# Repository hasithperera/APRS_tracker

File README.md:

# APRS_tracker

Standalone APRS tracker. This an Arduino-nano powered APRS tracker with a DRA818V 1 W radio module.

## Progress

- Fully functional PCB(v2) - tested up to 11 km in a HAB flight
- Basic full operation was tested with the board externally powered. Refer the test section for details.
- v3: Nearly complete PCB with new GPS module
	- level shifter externally added using a 7404 

### Firmware

- [x] Bug fix for location packets
- [x] Support for GNSS GPS (Adafruit GPS) ✅ 2024-01-28
- [x] Added support for i2c for external data sources ✅ 2024-01-28
## Testing 

In order to make sure the full functionality the generated APRS packets were tested with [direwolf](https://github.com/wb2osz/direwolf) with a RTL-SDR.
The following command was used to run the iGate

``` rtl_fm -f 144.39M - |direwolf -c sdr.conf -r 24000 -D 1 - ```

- The radio tx frequency commands were tested on a simplex 145.390 M and the standard 144.390 M
- A ground test was carried out on 05/14/23.
	- Device was powered with a external 5V USB power bank for the duration of the test
	- initial GPS lock was completed within 30 s of powering on outside.
	- It was noted that powering indoor and moving to an outdoor location increased the initial GPS lock time significantly.
	- Data collected is available online under the call sign KC3RXZ. a screenshot can be found below. Note that not all the packets were captured by the iGate and the msg_id was used as a counter for how many GPS packets were captured during the test period.Given that the iGate was located indoor and the landscape of the location could account for the lost packets.

APRS ground testing.

### Flight testing

- First HAB flight on 01/10/2023
- call: KE8TJE-11
- data: [aprs.fi](https://aprs.fi/#!mt=roadmap&z=10&call=a%2FKE8TJE-11&timerange=21600&tail=21600)
- comments: The GPS module used worked well up to 11 km of altitude. above that it was unusable
- more information available [here](https://docs.google.com/presentation/d/1fhy-rmdOGR4Q17i7Nnw9TJokxQfwU8tR1A3V_ZNNeEo/edit?usp=sharing) including flight data

## Updates to the PCB

### update: 05/07/23

- [x] Update PCB based on v1.
- know minor issues
	- jumpers on the board need to be larger

### update: October 2023

- updated the GPS module

### update: January 2034
- New design with an expansion slot to connect external modules.
- A DTMF decoder board is been developed.
- [ ] Final integration testing needs to be done

## Todo list 

- [x] interface GPS sensor
- [x] interface RF
- [x] APRS generation
- [x] get location and update APRS data packet
- [x] i2c slave module to provide data to master ✅ 2024-01-28
- [x] field testing 
- [x] finalized PCB design 
- [x] long range testing at altitude

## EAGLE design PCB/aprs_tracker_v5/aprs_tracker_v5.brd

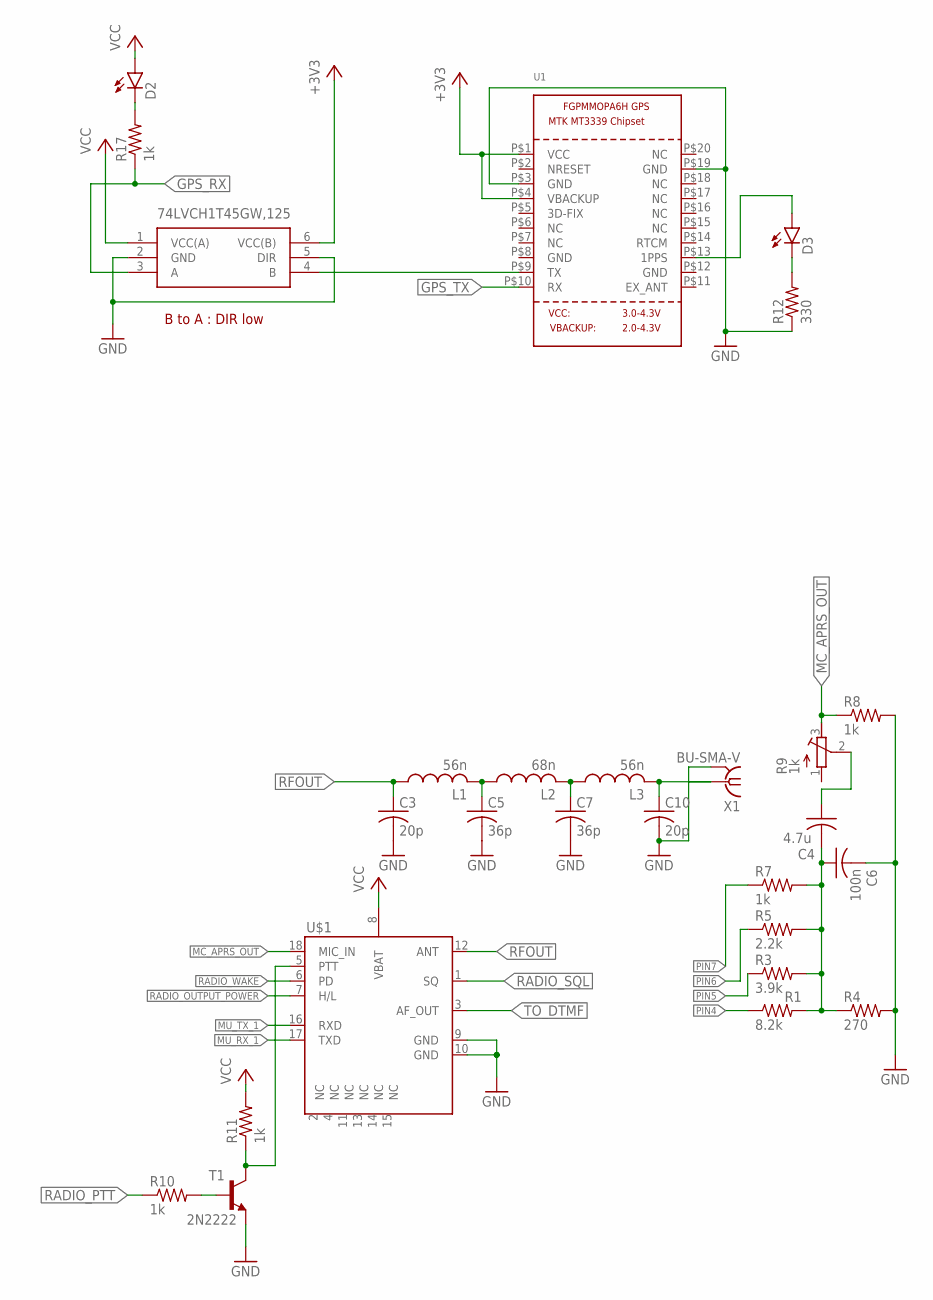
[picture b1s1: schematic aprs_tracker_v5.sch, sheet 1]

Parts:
C3, C10: 20p; C0805K
C4: 4.7u; C0805
C5, C7: 36p; C0805K
C6: 100n; C0805
D2, D3: LEDCHIP-LED0805; CHIP-LED0805
IC3: 74LVCH1T45GW,125; 74LVCH1T45GW125
L1, L3: 56n; L3216C
L2: 68n; L3216C
R1: 8.2k; R0805
R3: 3.9k; R0805
R4: 270; R0805
R5: 2.2k; R0805
R7, R8, R10, R11, R17: 1k; R0805
R9: 1k; RTRIM3339P
R12: 330; R0805
T1: 2N2222; TO92-EBC-OVAL
U1: GPS_FGPMMOPA6H; FGPMMOPA6H
U$1: DRA818A
X1: BU-SMA-V

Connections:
+3V3: IC3.6 (VCC(B)), U1.P$1 (VCC), U1.P$4 (VBACKUP); also elsewhere on the board
GND: C3.2, C5.2, C6.2, C7.2, C10.2, IC3.2 (GND), IC3.5 (DIR), R4.2, R8.2, R12.1, T1.E, U1.P$3 (GND), U1.P$19 (GND), U$1.9 (GND), U$1.10 (GND), X1.2, X1.3 (2), X1.4 (2), X1.5 (2); also elsewhere on the board
GPS_RX: IC3.3 (A), R17.1; also elsewhere on the board
GPS_TX: U1.P$10 (RX); also elsewhere on the board
MC_APRS_OUT: R8.1, R9.3 (E), U$1.18 (MIC_IN); also elsewhere on the board
MU_RX_1: U$1.17 (TXD); also elsewhere on the board
MU_TX_1: U$1.16 (RXD); also elsewhere on the board
unnamed: IC3.4 (B), U1.P$9 (TX)
unnamed: C5.1, L1.2, L2.1
unnamed: C7.1, L2.2, L3.1
unnamed: C10.1, L3.2, X1.1
unnamed: D2.C, R17.2
unnamed: C4.2, C6.1, R1.2, R3.2, R4.1, R5.2, R7.2
unnamed: C4.1, R9.2 (S)
unnamed: R11.1, T1.C, U$1.5 (PTT)
unnamed: R10.2, T1.B
unnamed: D3.C, R12.2
unnamed: D3.A, U1.P$13 (1PPS)
PIN4: R1.1; also elsewhere on the board
PIN5: R3.1; also elsewhere on the board
PIN6: R5.1; also elsewhere on the board
PIN7: R7.1; also elsewhere on the board
RADIO_OUTPUT_POWER: U$1.7 (H/L); also elsewhere on the board
RADIO_PTT: R10.1; also elsewhere on the board
RADIO_SQL: U$1.1 (SQ); also elsewhere on the board
RADIO_WAKE: U$1.6 (PD); also elsewhere on the board
RFOUT: C3.1, L1.1, U$1.12 (ANT)
TO_DTMF: U$1.3 (AF_OUT); also elsewhere on the board
VCC: D2.A, IC3.1 (VCC(A)), R11.2, U$1.8 (VBAT); also elsewhere on the board

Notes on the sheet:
B to A : DIR low

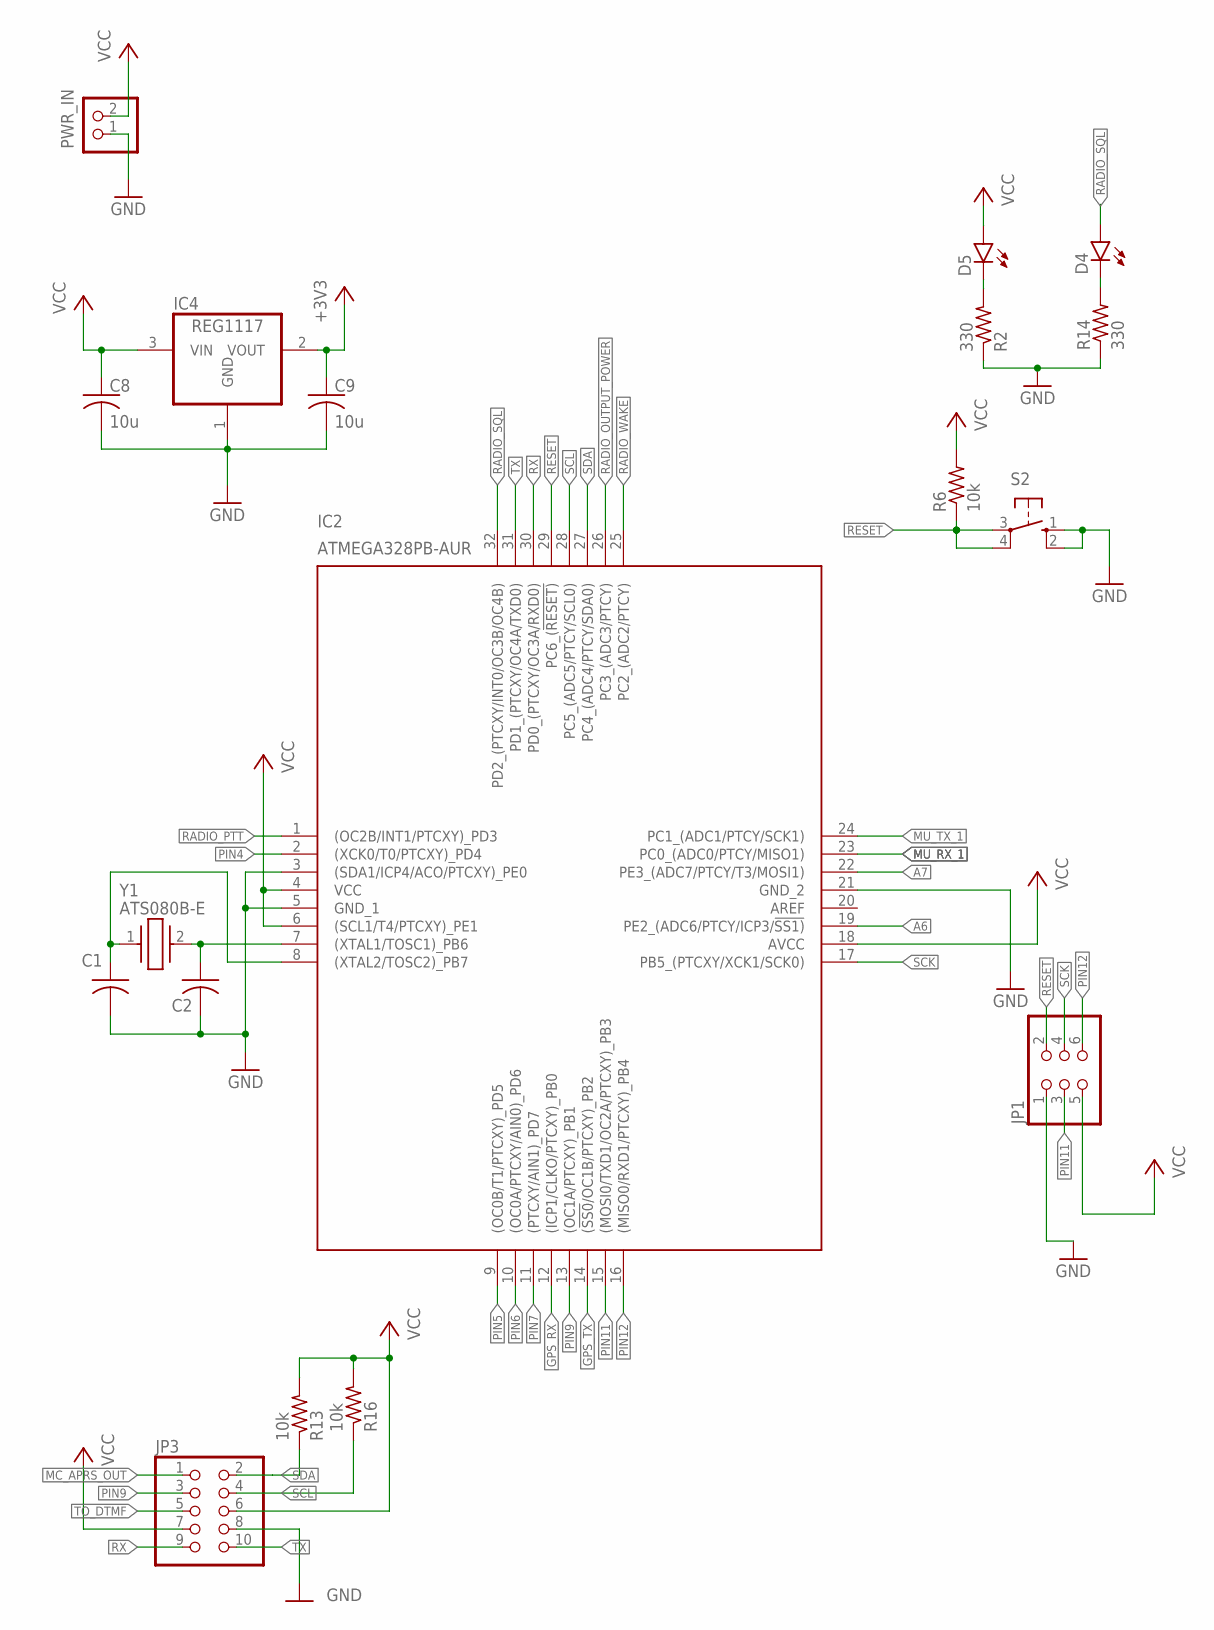
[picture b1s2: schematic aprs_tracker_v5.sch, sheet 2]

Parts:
C1, C2: C-USC0805; C0805
C8, C9: 10u; C0805
D4, D5: LEDCHIP-LED0805; CHIP-LED0805
IC2: ATMEGA328PB-AUR; QFP80P900X900X120-32N
IC4: REG1117; SOT223
JP1: PINHD-2X3; 2X03
JP3: PINHD-2X5; 2X05
PWR_IN: PINHD-1X2; 1X02
R2, R14: 330; R0805
R6, R13, R16: 10k; R0805
S2: 10-XX; B3F-10XX
Y1: ATS080B-E; ATS080BE

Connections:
+3V3: C9.1, IC4.2 (VOUT); also elsewhere on the board
A6: IC2.19 (PE2_(ADC6/PTCY/ICP3/!SS1))
A7: IC2.22 (PE3_(ADC7/PTCY/T3/MOSI1))
GND: C1.2, C2.2, C8.2, C9.2, IC2.3 ((SDA1/ICP4/ACO/PTCXY)_PE0), IC2.5 (GND_1), IC2.21 (GND_2), IC4.1 (GND), JP1.1, JP3.8, PWR_IN.1, R2.1, R14.1, S2.1 (S), S2.2 (S1); also elsewhere on the board
GPS_RX: IC2.12 ((ICP1/CLKO/PTCXY)_PB0); also elsewhere on the board
GPS_TX: IC2.14 ((!SS0!/OC1B/PTCXY)_PB2); also elsewhere on the board
MC_APRS_OUT: JP3.1; also elsewhere on the board
MU_RX_1: IC2.23 (PC0_(ADC0/PTCY/MISO1)); also elsewhere on the board
MU_TX_1: IC2.24 (PC1_(ADC1/PTCY/SCK1)); also elsewhere on the board
unnamed: D5.C, R2.2
unnamed: C1.1, IC2.8 ((XTAL2/TOSC2)_PB7), Y1.1
unnamed: C2.1, IC2.7 ((XTAL1/TOSC1)_PB6), Y1.2
unnamed: D4.C, R14.2
PIN4: IC2.2 ((XCK0/T0/PTCXY)_PD4); also elsewhere on the board
PIN5: IC2.9 ((OC0B/T1/PTCXY)_PD5); also elsewhere on the board
PIN6: IC2.10 ((OC0A/PTCXY/AIN0)_PD6); also elsewhere on the board
PIN7: IC2.11 ((PTCXY/AIN1)_PD7); also elsewhere on the board
PIN9: IC2.13 ((OC1A/PTCXY)_PB1), JP3.3
PIN11: IC2.15 ((MOSI0/TXD1/OC2A/PTCXY)_PB3), JP1.3
PIN12: IC2.16 ((MISO0/RXD1/PTCXY)_PB4), JP1.6
RADIO_OUTPUT_POWER: IC2.26 (PC3_(ADC3/PTCY)); also elsewhere on the board
RADIO_PTT: IC2.1 ((OC2B/INT1/PTCXY)_PD3); also elsewhere on the board
RADIO_SQL: D4.A, IC2.32 (PD2_(PTCXY/INT0/OC3B/OC4B)); also elsewhere on the board
RADIO_WAKE: IC2.25 (PC2_(ADC2/PTCY)); also elsewhere on the board
RESET: IC2.29 (PC6_(!RESET)), JP1.2, R6.1, S2.3, S2.4 (P1)
RX: IC2.30 (PD0_(PTCXY/OC3A/RXD0)), JP3.9
SCK: IC2.17 (PB5_(PTCXY/XCK1/SCK0)), JP1.4
SCL: IC2.28 (PC5_(ADC5/PTCY/SCL0)), JP3.4, R16.1
SDA: IC2.27 (PC4_(ADC4/PTCY/SDA0)), JP3.2, R13.1
TO_DTMF: JP3.5; also elsewhere on the board
TX: IC2.31 (PD1_(PTCXY/OC4A/TXD0)), JP3.10
VCC: C8.1, D5.A, IC2.4 (VCC), IC2.6 ((SCL1/T4/PTCXY)_PE1), IC2.18 (AVCC), IC4.3 (VIN), JP1.5, JP3.6, JP3.7, PWR_IN.2, R6.2, R13.2, R16.2; also elsewhere on the board

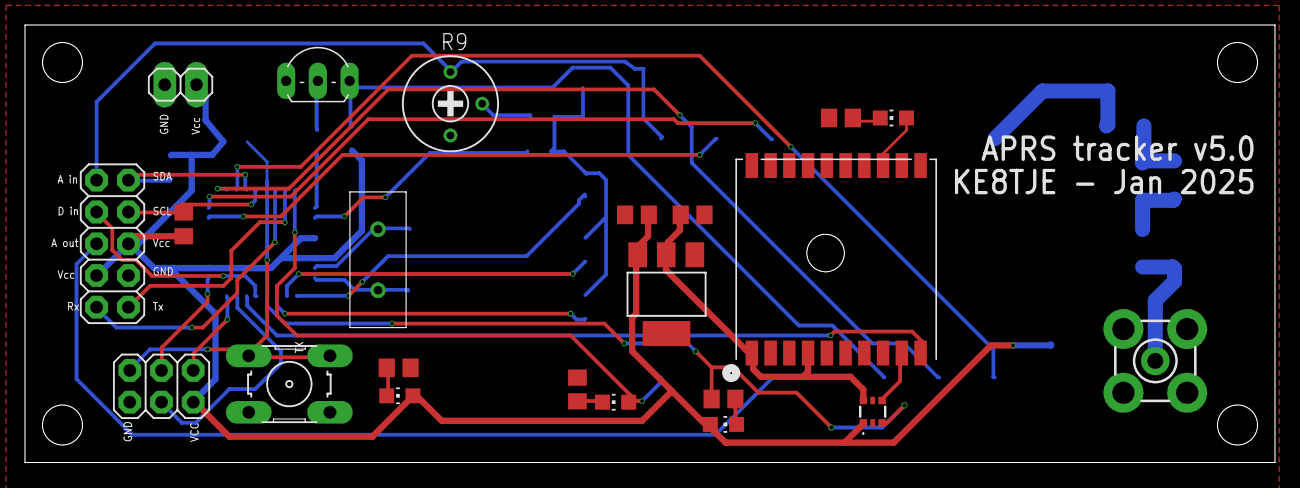
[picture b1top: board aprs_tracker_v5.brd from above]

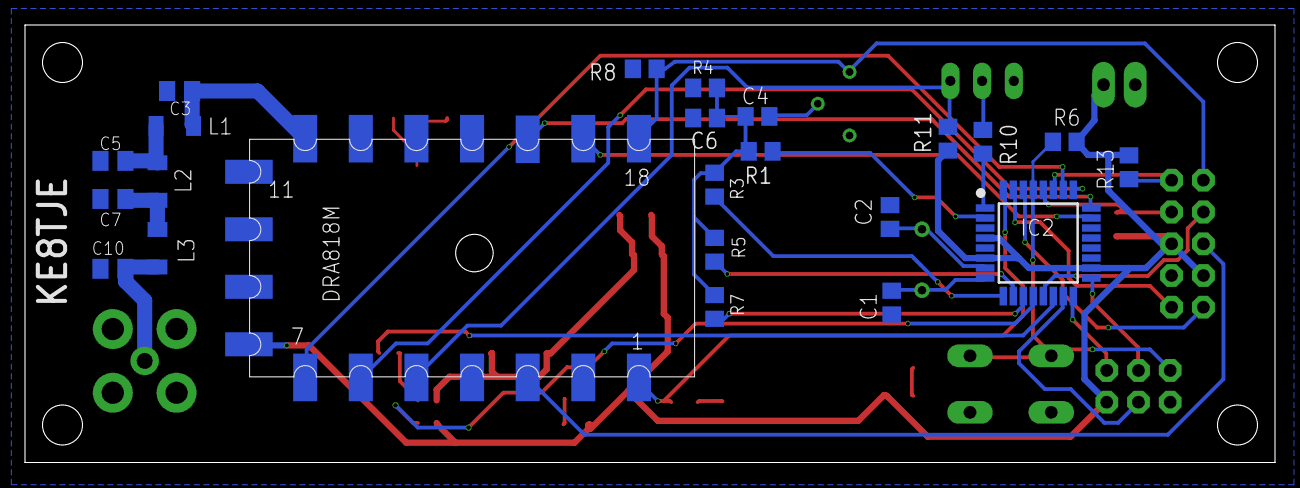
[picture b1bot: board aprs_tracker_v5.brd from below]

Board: 2 copper layers, 100.0 x 35.0 mm, 45 parts (23 on the bottom side), 42 nets.

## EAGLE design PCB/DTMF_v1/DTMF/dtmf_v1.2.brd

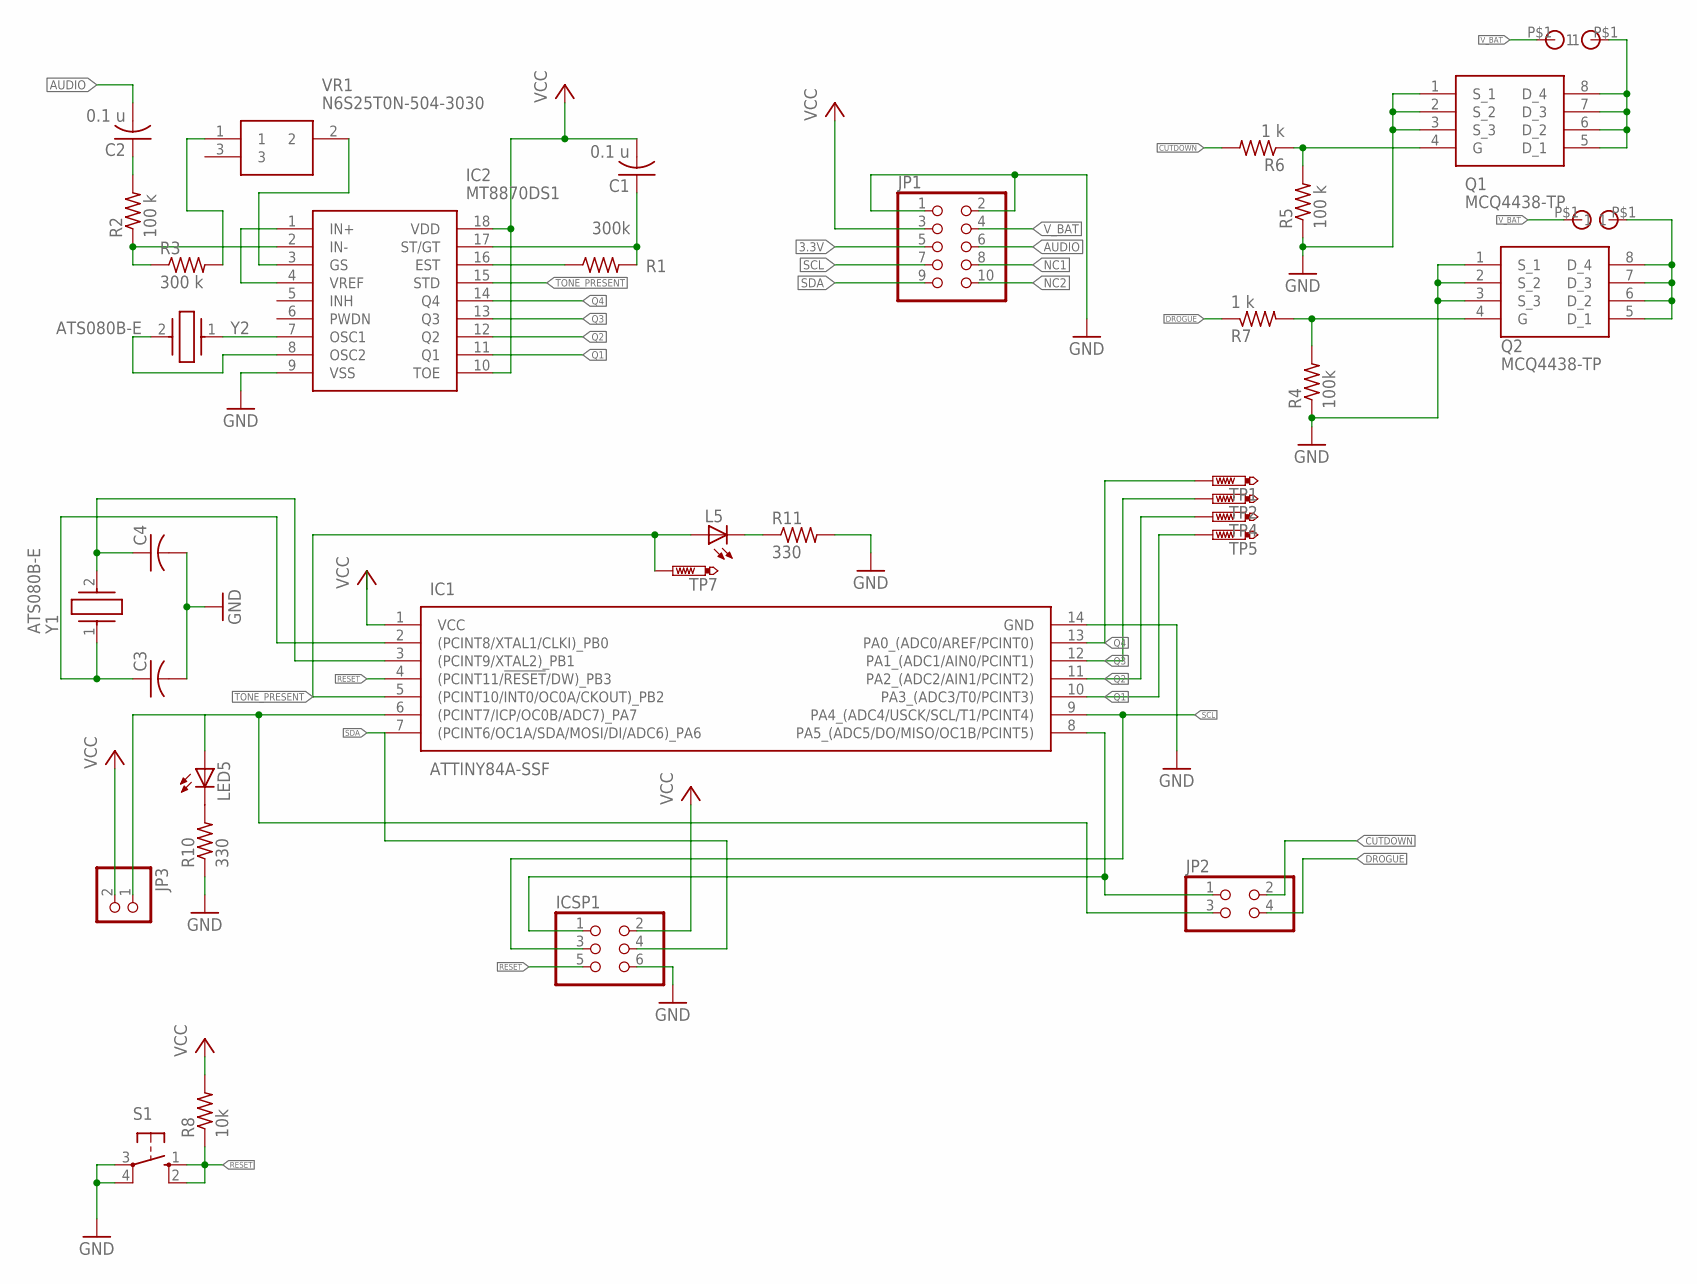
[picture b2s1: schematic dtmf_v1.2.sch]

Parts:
C1, C2: 0.1 u; C0603
C3, C4: C-USC0805; C0805
IC1: ATTINY84A-SSF; SOIC127P600X175-14N
IC2: MT8870DS1; SOIC127P1032X265-18N
ICSP1: PINHD-2X3; 2X03
JP1: PINHD-2X5; 2X05
JP2: PINHD-2X2; 2X02
JP3: PINHD-1X2; 1X02
L5: LEDCHIP-LED0805; CHIP-LED0805
LED5: LEDCHIP-LED0805; CHIP-LED0805
Q1, Q2: MCQ4438-TP; SOIC127P600X175-8N
R1: 300k; M0805
R2, R5: 100 k; M0805
R3: 300 k; M0805
R4: 100k; M0805
R6, R7: 1 k; M0805
R8: 10k; 0207/10
R10, R11: 330; M0805
S1: 10-XX; B3F-10XX
TP1, TP2, TP4, TP5, TP7: PTR1B1,27; B1,27
U$1, U$2, U$3, U$4: M3_HOLE; MOUNTING_PAD
VR1: N6S25T0N-504-3030; N6S25T0N5043030
Y1, Y2: ATS080B-E; ATS080BE

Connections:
3.3V: JP1.5
AUDIO: C2.2, JP1.6
CUTDOWN: JP2.2, R6.2
DROGUE: JP2.4, R7.1
GND: C3.2, C4.2, IC1.14 (GND), IC2.9 (VSS), ICSP1.6, JP1.1, JP1.2, Q1.1 (S_1), Q1.2 (S_2), Q1.3 (S_3), Q2.1 (S_1), Q2.2 (S_2), Q2.3 (S_3), R4.1, R5.1, R10.1, R11.2, S1.3, S1.4 (P1)
unnamed: IC2.7 (OSC1), Y2.1
unnamed: IC2.8 (OSC2), Y2.2
unnamed: IC2.1 (IN+), IC2.4 (VREF)
unnamed: Q1.4 (G), R5.2, R6.1
unnamed: C3.1, IC1.2 ((PCINT8/XTAL1/CLKI)_PB0), Y1.1
unnamed: C4.1, IC1.3 ((PCINT9/XTAL2)_PB1), Y1.2
unnamed: C1.1, IC2.17 (ST/GT), R1.2
unnamed: IC2.16 (EST), R1.1
unnamed: R3.2, VR1.1
unnamed: IC2.2 (IN-), R2.1, R3.1
unnamed: C2.1, R2.2
unnamed: IC2.3 (GS), VR1.2
unnamed: Q2.5 (D_1), Q2.6 (D_2), Q2.7 (D_3), Q2.8 (D_4), U$4.P$1
unnamed: Q1.5 (D_1), Q1.6 (D_2), Q1.7 (D_3), Q1.8 (D_4), U$2.P$1
unnamed: IC1.6 ((PCINT7/ICP/OC0B/ADC7)_PA7), JP2.3, JP3.1, LED5.A
unnamed: LED5.C, R10.2
unnamed: IC1.8 (PA5_(ADC5/DO/MISO/OC1B/PCINT5)), ICSP1.1, JP2.1
unnamed: L5.C, R11.1
unnamed: Q2.4 (G), R4.2, R7.2
NC1: JP1.8
NC2: JP1.10
Q1: IC1.10 (PA3_(ADC3/T0/PCINT3)), IC2.11 (Q1), TP5.TP
Q2: IC1.11 (PA2_(ADC2/AIN1/PCINT2)), IC2.12 (Q2), TP4.TP
Q3: IC1.12 (PA1_(ADC1/AIN0/PCINT1)), IC2.13 (Q3), TP2.TP
Q4: IC1.13 (PA0_(ADC0/AREF/PCINT0)), IC2.14 (Q4), TP1.TP
RESET: IC1.4 ((PCINT11/!RESET!/DW)_PB3), ICSP1.5, R8.1, S1.1 (S), S1.2 (S1)
SCL: IC1.9 (PA4_(ADC4/USCK/SCL/T1/PCINT4)), ICSP1.3, JP1.7
SDA: IC1.7 ((PCINT6/OC1A/SDA/MOSI/DI/ADC6)_PA6), ICSP1.4, JP1.9
TONE_PRESENT: IC1.5 ((PCINT10/INT0/OC0A/CKOUT)_PB2), IC2.15 (STD), L5.A, TP7.TP
VCC: C1.2, IC1.1 (VCC), IC2.10 (TOE), IC2.18 (VDD), ICSP1.2, JP1.3, JP3.2, R8.2
V_BAT: JP1.4, U$1.P$1, U$3.P$1

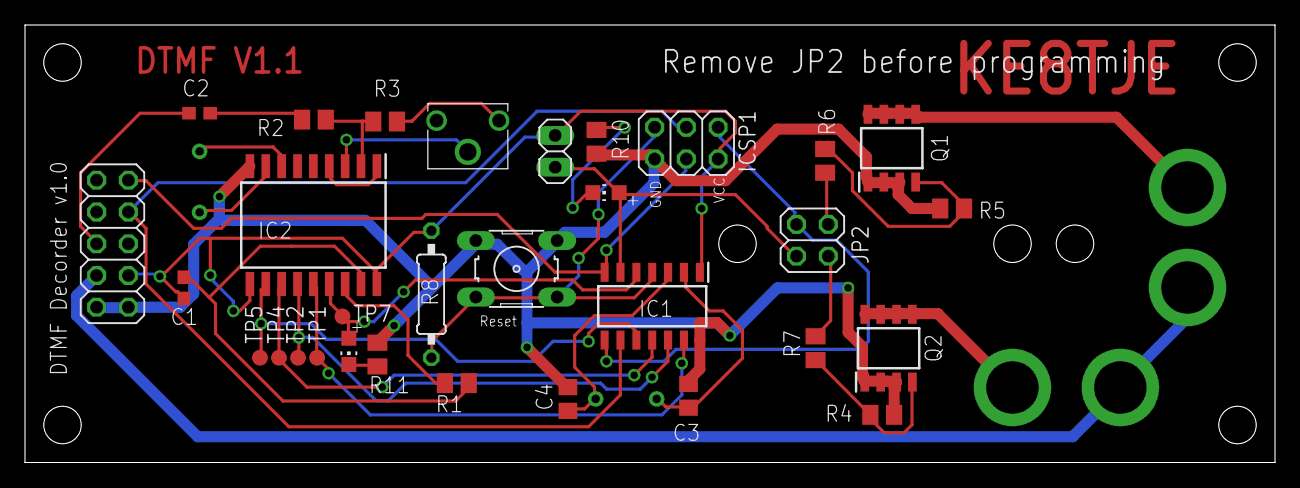
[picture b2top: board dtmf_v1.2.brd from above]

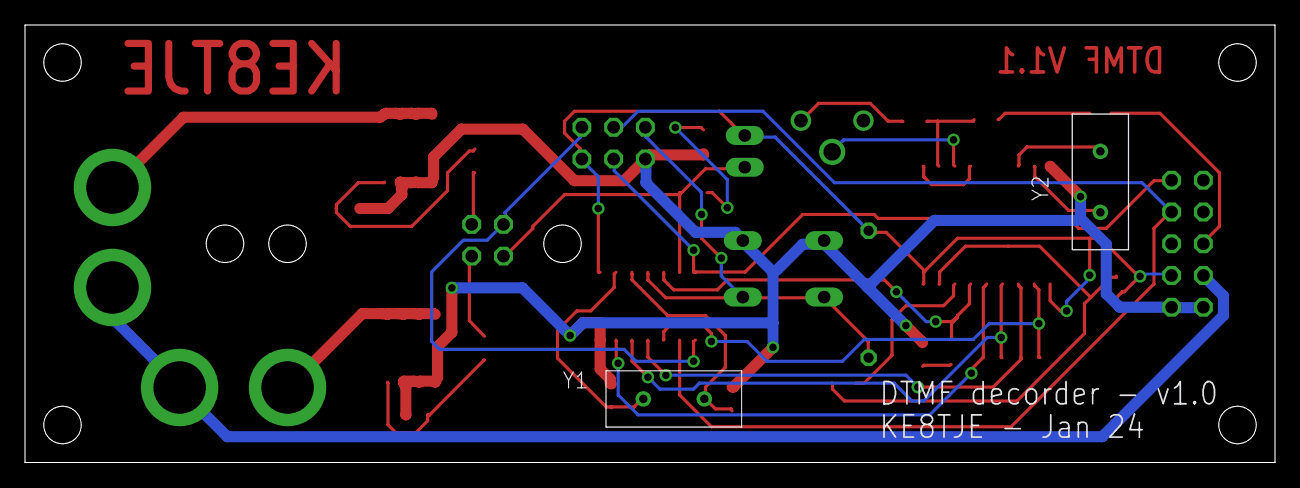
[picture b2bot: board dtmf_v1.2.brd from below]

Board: 2 copper layers, 100.0 x 35.0 mm, 37 parts (2 on the bottom side), 33 nets.

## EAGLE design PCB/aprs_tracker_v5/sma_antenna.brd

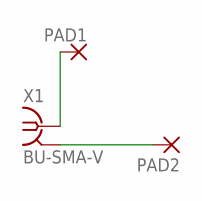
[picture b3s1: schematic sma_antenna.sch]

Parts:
PAD1, PAD2: 3,81/1,4
X1: BU-SMA-V

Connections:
unnamed: PAD1.1, X1.1
unnamed: PAD2.1, X1.2, X1.3 (2), X1.4 (2), X1.5 (2)

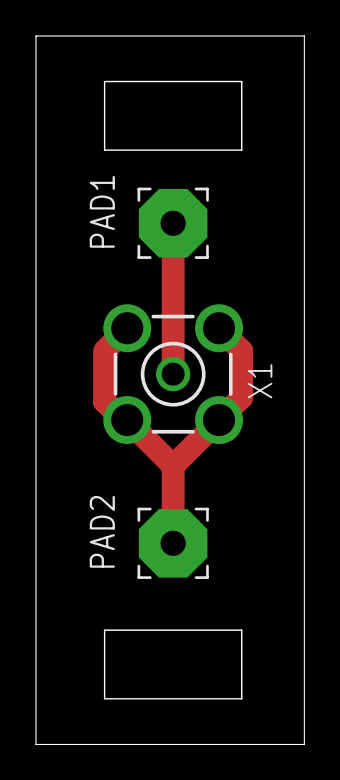
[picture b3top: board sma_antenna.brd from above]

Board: 2 copper layers, 14.8 x 39.3 mm, 3 parts (0 on the bottom side), 2 nets.

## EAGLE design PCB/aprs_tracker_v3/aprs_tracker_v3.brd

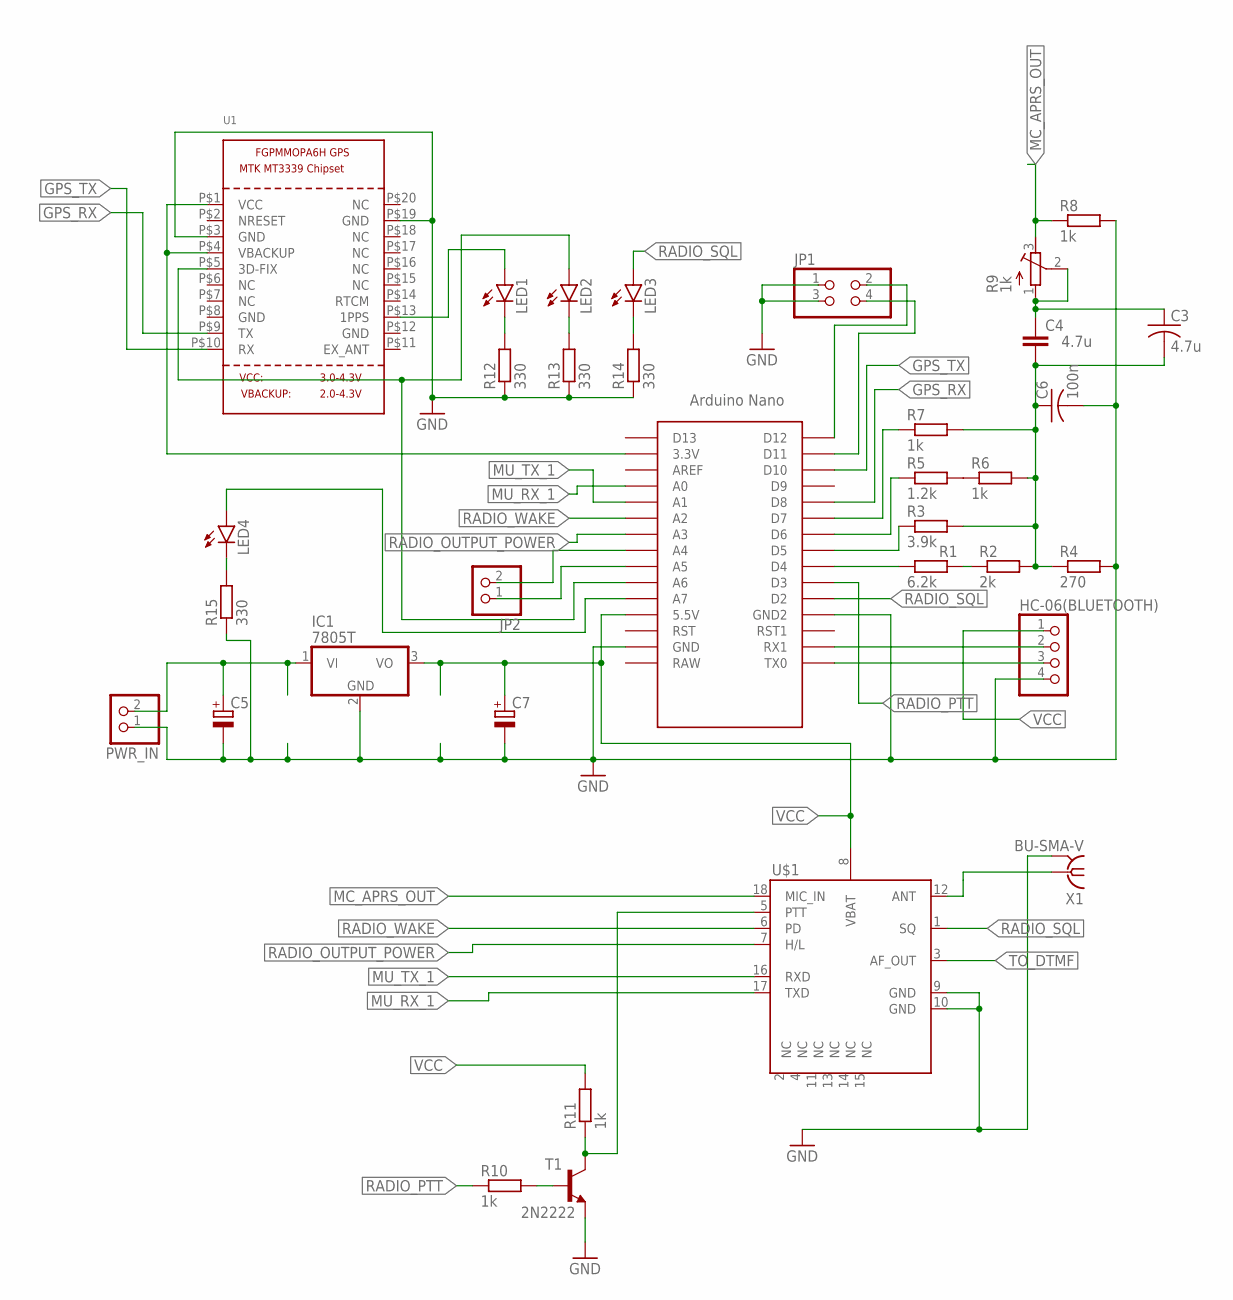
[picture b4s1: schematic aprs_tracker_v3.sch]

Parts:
C3: 4.7u; C050-024X044
C4: 4.7u; C1206
C5, C7: CPOL-EUE5-6; E5-6
C6: 100n; C050-024X044
HC-06(BLUETOOTH): PINHD-1X4; 1X04
IC1: 7805T; TO220H
JP1: PINHD-2X2; 2X02
JP2: PINHD-1X2; 1X02
LED1, LED2, LED3, LED4: LEDCHIP-LED0805; CHIP-LED0805
PWR_IN: PINHD-1X2; 1X02
R1: 6.2k; 0207/7
R2: 2k; 0207/7
R3: 3.9k; 0207/7
R4: 270; 0204/7
R5: 1.2k; 0207/7
R6, R7, R10, R11: 1k; 0207/7
R8: 1k; 0207/12
R9: 1k; RTRIM3339P
R12, R13, R14, R15: 330; R0805
T1: 2N2222; TO92-EBC-OVAL
U1: GPS_FGPMMOPA6H; FGPMMOPA6H
U$1: DRA818A
U$4: NANO-2; NANO-NOICSP
X1: BU-SMA-V

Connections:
GND: C5.-, C6.2, C7.-, HC-06(BLUETOOTH).4, IC1.2 (GND), JP1.1, JP1.3, PWR_IN.1, R4.2, R8.2, R12.1, R13.1, R14.1, R15.1, T1.E, U1.P$3 (GND), U1.P$19 (GND), U$1.9 (GND), U$1.10 (GND), U$4.GND, U$4.GND1 (GND2), X1.2, X1.3 (2), X1.4 (2), X1.5 (2)
GPS_RX: U1.P$9 (TX), U$4.D8
GPS_TX: U1.P$10 (RX), U$4.D10
MC_APRS_OUT: R8.1, R9.3 (E), U$1.18 (MIC_IN)
MU_RX_1: U$1.17 (TXD), U$4.A0
MU_TX_1: U$1.16 (RXD), U$4.A1
unnamed: U$1.12 (ANT), X1.1
unnamed: C5.+, IC1.1 (VI), PWR_IN.2
unnamed: HC-06(BLUETOOTH).2, U$4.RX1
unnamed: R1.1, U$4.D4
unnamed: R3.1, U$4.D5
unnamed: R5.1, U$4.D6
unnamed: R7.1, U$4.D7
unnamed: R1.2, R2.1
unnamed: R5.2, R6.1
unnamed: C3.2, C4.2, C6.1, R2.2, R3.2, R4.1, R6.2, R7.2
unnamed: C3.1, C4.1, R9.1 (A), R9.2 (S)
unnamed: R11.1, T1.C, U$1.5 (PTT)
unnamed: HC-06(BLUETOOTH).3, U$4.TX0
unnamed: R10.2, T1.B
unnamed: JP1.2, U$4.D12
unnamed: JP1.4, U$4.D11
unnamed: JP2.1, U$4.A5
unnamed: JP2.2, U$4.A4
unnamed: U1.P$1 (VCC), U1.P$4 (VBACKUP), U$4.3.3V
unnamed: LED1.C, R12.2
unnamed: LED2.C, R13.2
unnamed: LED3.C, R14.2
unnamed: LED1.A, U1.P$13 (1PPS)
unnamed: LED4.C, R15.2
unnamed: LED4.A, U$4.A7
unnamed: LED2.A, U1.P$5 (3D-FIX), U$4.A6
RADIO_OUTPUT_POWER: U$1.7 (H/L), U$4.A3
RADIO_PTT: R10.1, U$4.D3
RADIO_SQL: LED3.A, U$1.1 (SQ), U$4.D2
RADIO_WAKE: U$1.6 (PD), U$4.A2
TO_DTMF: U$1.3 (AF_OUT)
VCC: C7.+, HC-06(BLUETOOTH).1, IC1.3 (VO), R11.2, U$1.8 (VBAT), U$4.5V (5.5V)

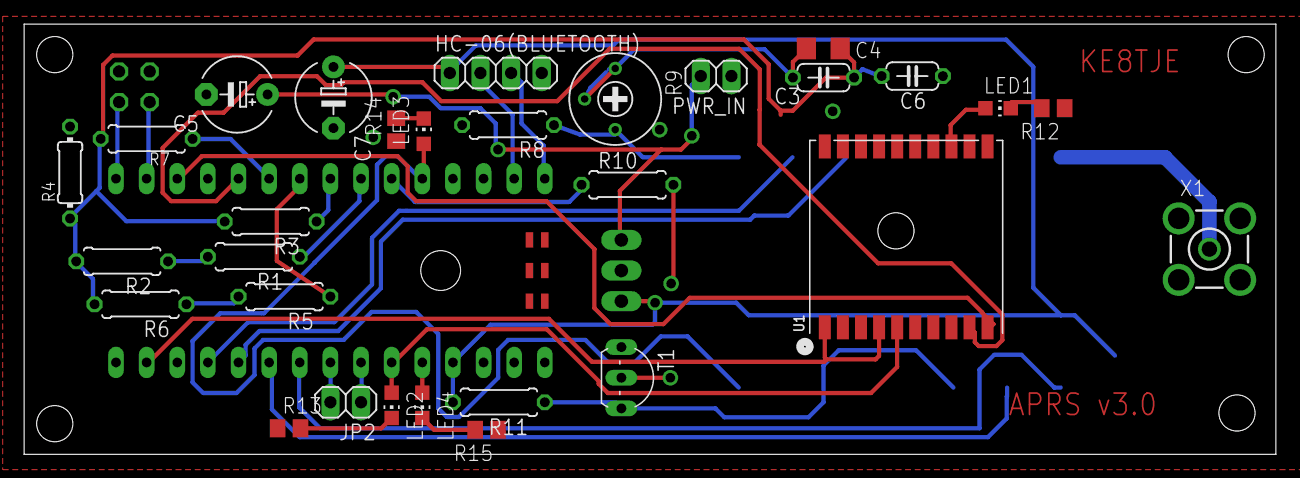
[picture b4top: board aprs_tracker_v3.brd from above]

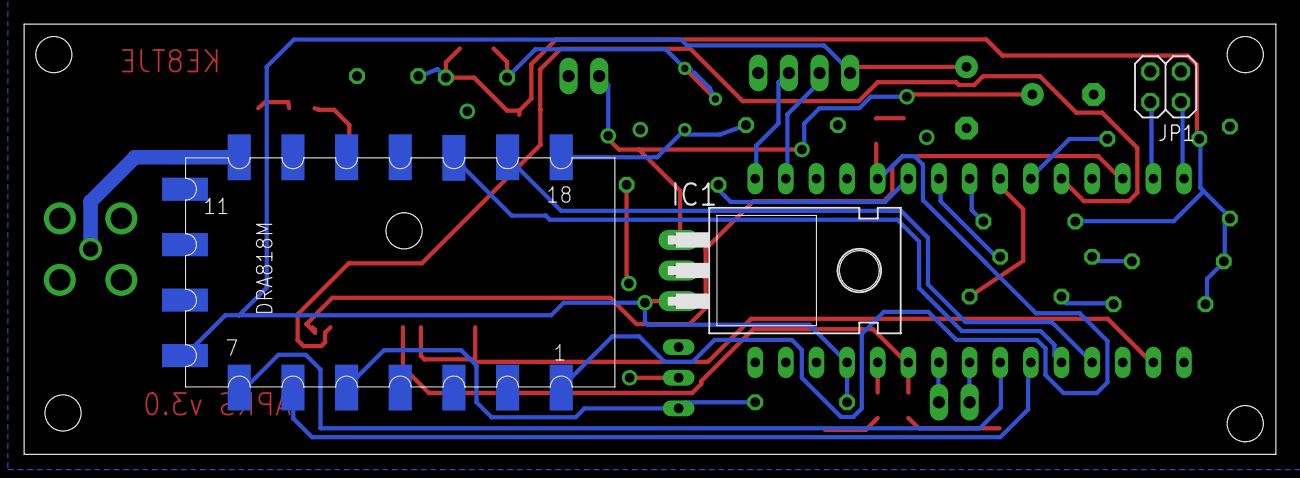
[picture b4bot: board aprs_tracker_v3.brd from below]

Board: 2 copper layers, 103.8 x 35.7 mm, 34 parts (3 on the bottom side), 37 nets.

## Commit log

2023-05-14 initial working code with all features. (GPS + RF + APRS)
2023-05-14 updated the readme
2023-05-14 Added GPS module test data for processing
2023-05-14 final version before the ground test
2023-05-14 updated the documentation and final fixes to a msg valid flag for GPS data
2023-05-14 added the libraries used for the project
2023-05-17 Added new features - busy channel detection and hold until clear - alternate frequency setting
2023-05-17 added simulation preproc commands and better serial prints
2023-05-17 Tested version
2023-05-17 added external pins for settings
2023-05-18 bug fix for the string memory issue
2023-05-18 Bug fix on the memory error
2023-07-06 Added v2.2 PCB
2023-07-06 added v2.2 PCB and readme updates
2023-07-06 added doc pcb image
2023-07-06 fixed the readme
2023-07-14 added changes to have one jumper always in the selection switches
2023-07-18 added sdr.conf file
2023-08-19 final working version without alt
2023-08-19 added altitude and horizontal error
2023-09-30 added altitude and sdr,YAAC configuration
2023-10-01 added YAAC logs from 10/01 launch
2023-10-01 added APRS.fi logs from 10/01 launch
2023-10-04 added aprs data read python
2023-10-07 aprs v3.0 inital desin
2023-10-08 added finalized v3
2023-10-08 modified documentation to add flight data form 01/10/23
2023-10-08 Update README.md fixed spellins
2023-10-09 added BOM and final fixes
2023-10-11 v2 final code
2023-10-11 fixed the location update bug
2023-10-12 added raw packet strings as comments
2023-10-13 refactored code to add more settings
2023-10-13 bugged v3 code
2023-10-13 v3 GPS updated
2023-10-13 Final APRS v2: NEBP TX flight
2023-10-22 added v3 final code and data processing code
2023-12-05 added data from TX launch and modifed script for plotting
2023-12-24 added sql interupt - DTMF observations - sql pin is interfaced correctly
2023-12-24 added obsidianmd and new DTMF tone data
2023-12-24 added gitignore file and some docs
2023-12-24 vault backup: 2023-12-23 19:44:38
2023-12-24 vault backup: 2023-12-23 19:46:10
2023-12-24 vault backup: 2023-12-23 22:05:28
2023-12-24 vault backup: 2023-12-24 16:19:23
2023-12-26 Added DTMF v1.0 board and required libraries for eagle
2023-12-27 vault backup: 2023-12-27 10:32:53
2023-12-27 modifications done on mac for the board
2023-12-27 vault backup: 2023-12-27 18:42:20
2023-12-29 added eagle files and mods to the doc
2024-01-01 DTMF v1 completed with cutdown 30x100 mm form factor
2024-01-04 cleaned the schematic for documentation
2024-01-06 modified PCB with JLC DRC file
2024-01-06 vault backup: 2024-01-05 21:22:10
2024-01-07 added openhw log,slot for internal leds
2024-01-07 added atmega328p direct board APRS-v4
2024-01-07 vault backup: 2024-01-07 17:03:20
2024-01-07 vault backup: 2024-01-07 17:03:22
2024-01-08 final board design
2024-01-10 completed aprs v4
2024-01-10 fix 3v regulator location
2024-01-17 Added basic code and make file
2024-01-25 matching clock's with verified signals
2024-01-25 added basic functions to use i2c
2024-01-27 i2c compatible version - this has bugs. but had correct clocks - when i2c is a good starting point
2024-01-27 vault backup: 2024-01-27 01:28:47
2024-01-28 new i2c implementation. the arduino responded to the correct address. But data was not sent. possible ack/nak mismatch
2024-01-28 partially working i2c new function
2024-01-28 working i2c for single byte
2024-01-28 working dtmf commanding and mock cutdown finction
2024-01-28 Revert "Dtmf"
2024-01-28 added dtmf code form crash
2024-01-28 added i2c data read for the aprs tracker
2024-01-28 recoverd schematic files
2024-01-28 vault backup : 2024-01-28 17:36:03
2024-01-30 updates on audio testing
2024-01-30 recoverd tracker v3 file
2024-01-30 data folder recovered
2024-01-30 added mods to the docs to add old experiments
2024-01-30 add a git ignore file for common binary files
2024-01-30 fix the git ignore file
2024-02-06 added .gitignore file
2024-02-06 modfied the ignore file with comments and new formats
2024-02-10 added avrdude cmd to program v4
2024-02-11 v4 working atlitude packet decording
2024-02-11 tested version for v4 board. atl,main and rx confirmed
2024-02-11 added docs for class
2024-02-11 vault backup: 2024-02-11 16:34:21
2024-02-11 vault backup: 2024-02-11 18:26:25
2024-02-12 vault backup: 2024-02-12 10:23:15
2024-02-12 vault backup: 2024-02-12 10:26:32
2024-02-12 vault backup: 2024-02-12 10:27:03
2024-02-12 vault backup: 2024-02-12 10:49:44
2024-03-18 erros in aprs tx
2024-03-18 altitude bug fix
2024-03-18 vault backup: 2024-03-17 23:42:09
2024-03-20 vault backup: 2024-03-20 08:58:21
2024-03-21 dtmf with status and reset commands
2024-03-21 working v4.3
2024-06-27 added 2m dipole adapter
2024-12-25 added v5 board
2024-12-28 added 10k res to the i2c lines
2025-03-02 March 1 flight code
2025-03-22 update aprs main code to gps sync, needs testing
2025-03-22 added v5 final production PCB
2025-03-22 added schematic and PCB image
2025-03-22 formated altitude to telemetry like formatting
2025-03-22 updated the readme and cleaned unused code
2025-03-22 Update README.md
    added some instructions for the use
